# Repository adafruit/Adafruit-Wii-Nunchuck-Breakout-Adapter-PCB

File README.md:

## Adafruit Wii Nunchuck Breakout Adapter PCB

<a href="http://www.adafruit.com/products/4836"><br/>
Click here to purchase one from the Adafruit shop</a>

PCB files for the Adafruit Wii Nunchuck Breakout Adapter.

Format is EagleCAD schematic and board layout
* https://www.adafruit.com/product/4836

### Description

Dig out that old Wii controller and use it as a sleek controller for your next robot if you like. The Adafruit Adafruit Wii Nunchuck Breakout Adapter fits snugly into the Wii connector, and performs the level shifting and power regulation needed to use the controller with any microcontroller or microcomputer.

The Wii controllers use a standard I2C interface, and there's existing code for both Arduino and CircuitPython/Python for quick integration with an Arduino UNO, Feather, or even a Raspberry Pi. We like to use these with the Wii Nunchuck, as you can get an X-Y joystick, two buttons and an accelerometer all in one hand-held package. All data is transmitted over I2C address 0x52, and the address can not be changed.

We use extra thicc 2.0mm PCBs for this breakout, and made cut-outs for the grabber-notches, so that the controller connection is snug, and wont rattle or come loose!

To make using it as easy as possible, we’ve created this breakout in Stemma QT form factor. You can either use a breadboard or the SparkFun qwiic compatible STEMMA QT connectors, and compatibility with 5V voltage levels as commonly found on Arduinos, as well as 3.3V logic used by many other boards like the Raspberry Pi or our Feathers. QT Cable is not included, but we have a variety in the shop for quick plug-and-play support.

Doesn't come with the Wii Nunchuck controller, that's sold separately (or just look in that plastic bin in your parent's attic next time you visit).

### License

Adafruit invests time and resources providing this open source design, please support Adafruit and open-source hardware by purchasing products from [Adafruit](https://www.adafruit.com)!

Designed by Limor Fried/Ladyada for Adafruit Industries.

Creative Commons Attribution/Share-Alike, all text above must be included in any redistribution.
See license.txt for additional details.

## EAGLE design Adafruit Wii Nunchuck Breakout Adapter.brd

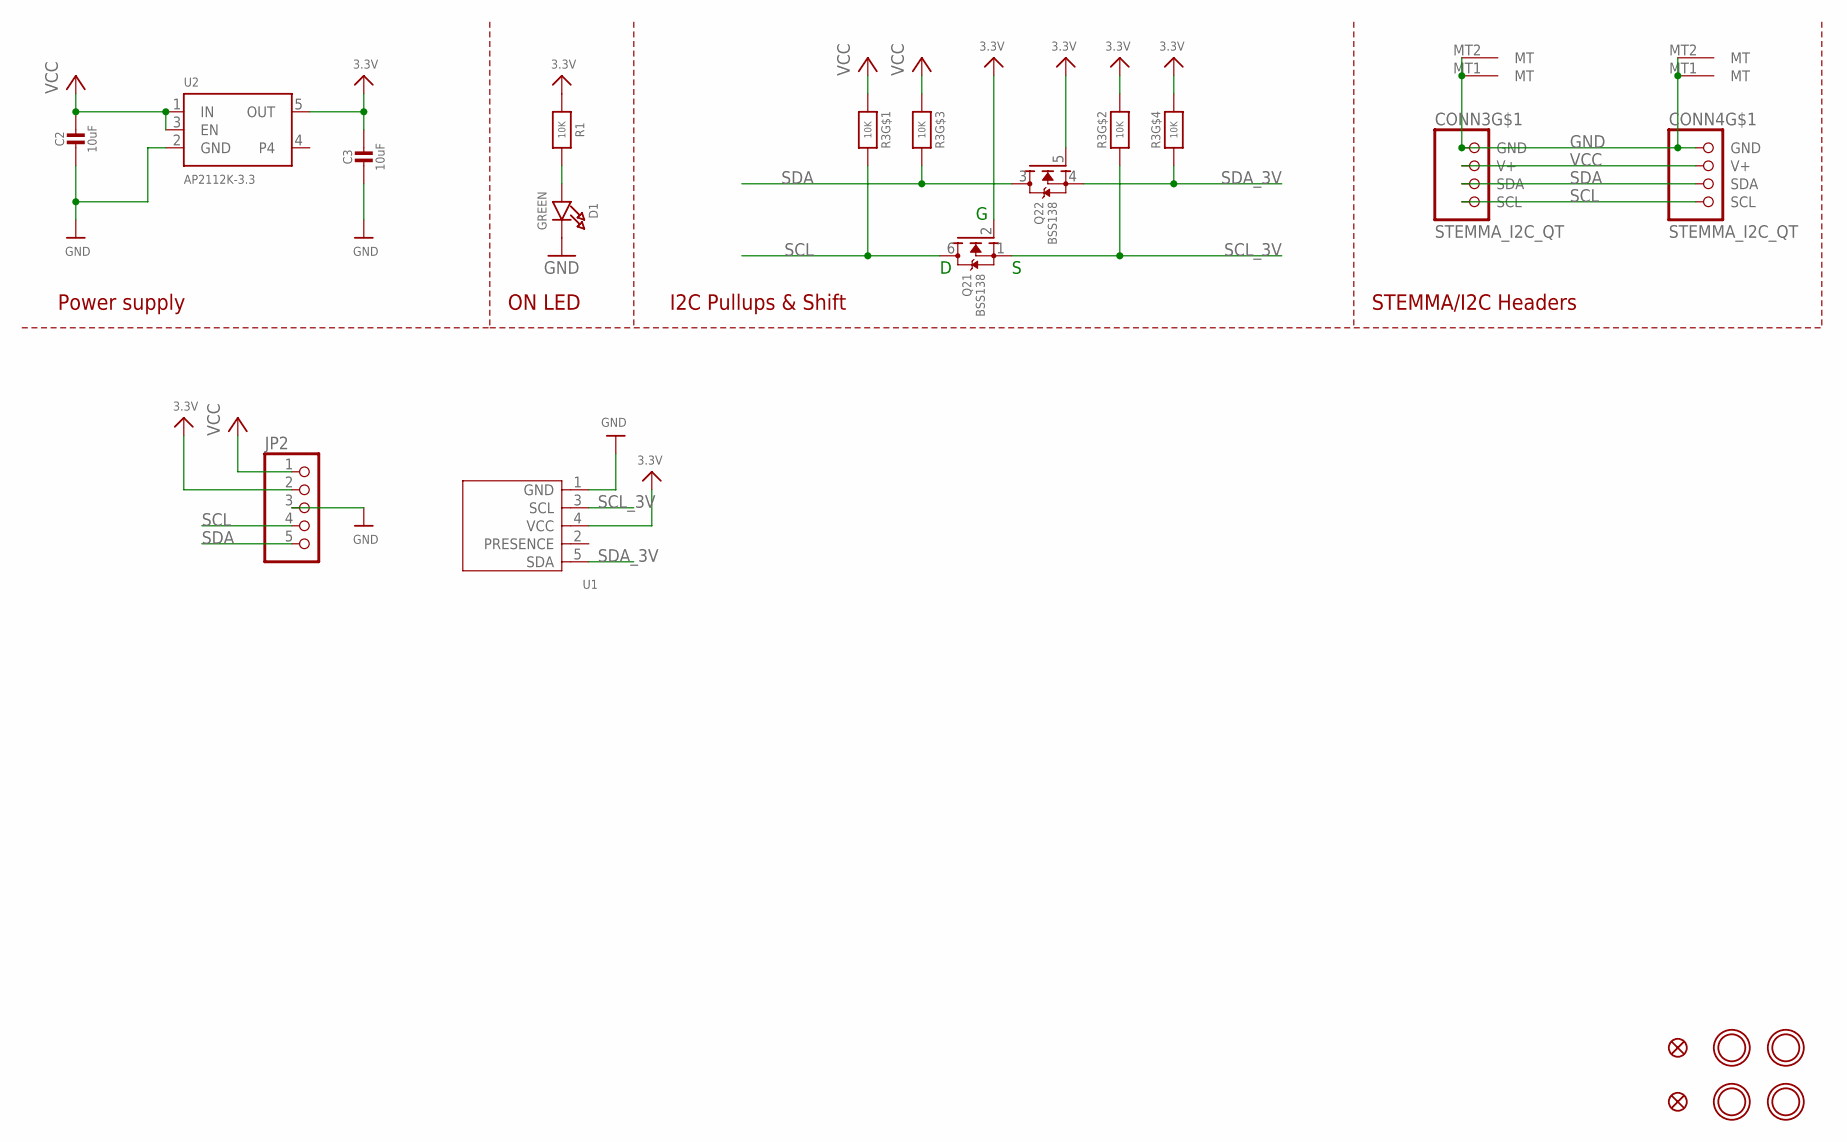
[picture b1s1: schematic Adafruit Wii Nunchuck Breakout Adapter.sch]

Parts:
C2, C3: 10uF; 0805-NO
CONN3, CONN4: STEMMA_I2C_QT; JST_SH4
D1: GREEN; CHIPLED_0603_NOOUTLINE
FID3, FID4: FIDUCIAL_1MM
JP2: HEADER-1X570MIL; 1X05_ROUND_70
Q2: BSS138; SOT363
R1: 10K; 0603-NO
R3: 10K; RESPACK_4X0603
U1: WIICHUCK
U2: AP2112K-3.3; SOT23-5
U$1, U$17, U$19, U$21: MOUNTINGHOLE2.5; MOUNTINGHOLE_2.5_PLATED

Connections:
3.3V: C3.1, JP2.2, Q2.2 (G), Q2.5 (G), R1.1, R3.2 (1), R3.4 (1), U1.4 (VCC), U2.5 (OUT)
GND: C2.2, C3.2, CONN3.1 (GND), CONN3.MT1 (MT), CONN3.MT2 (MT), CONN4.1 (GND), CONN4.MT1 (MT), CONN4.MT2 (MT), D1.C, JP2.3, U1.1 (GND), U2.2 (GND)
unnamed: D1.A, R1.2
SCL: CONN3.4 (SCL), CONN4.4 (SCL), JP2.4, Q2.6 (D), R3.8 (2)
SCL_3V: Q2.1 (S), R3.7 (2), U1.3 (SCL)
SDA: CONN3.3 (SDA), CONN4.3 (SDA), JP2.5, Q2.3 (D), R3.6 (2)
SDA_3V: Q2.4 (S), R3.5 (2), U1.5 (SDA)
VCC: C2.1, CONN3.2 (V+), CONN4.2 (V+), JP2.1, R3.1, R3.3 (1), U2.1 (IN), U2.3 (EN)

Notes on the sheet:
I2C Pullups & Shift
STEMMA/I2C Headers
ON LED
Power supply

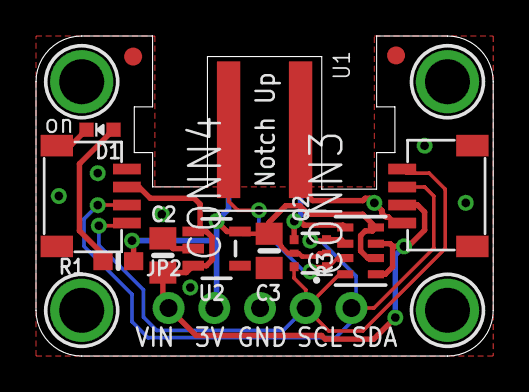
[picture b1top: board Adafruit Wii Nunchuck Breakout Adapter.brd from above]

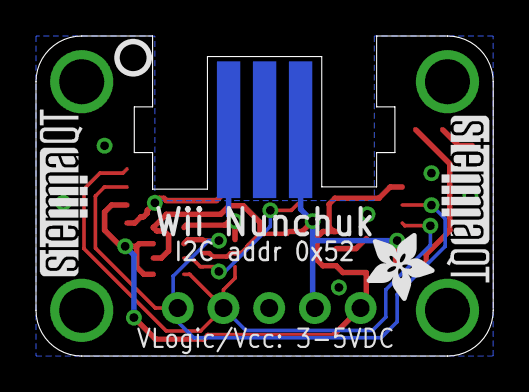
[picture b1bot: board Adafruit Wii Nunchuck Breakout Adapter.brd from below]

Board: 2 copper layers, 25.4 x 17.8 mm, 21 parts (4 on the bottom side), 8 nets.

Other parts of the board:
U$22: ADAFRUIT_3.5MM
U$25: PCBFEAT-REV-040
U$30, U$31: STEMMAQT

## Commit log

2020-12-09 adding board files.
2022-01-12 Changed typo'd I2C address from 0x53 to 0x52

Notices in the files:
parts and their libraries:
microbuilder: This work is placed in the public domain, and may be freely used for commercial and non-commercial work with the following conditions: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
